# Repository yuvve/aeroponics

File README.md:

# aeroponics

## Project Structure

. \
├── arduino \
│   └── Sensor example code written with PlatformIO \
├── design \
│   └── Buck-converter PCB files\
├── docs \
│   ├── Diagrams \
│   ├── Failure mode and effect analysis  \
│   └── Bill of materials \
├── ESPHome \
│   ├── Readme with ESPHome instructions \
│   └── ESPHome code for the microcontrollers \
├── OpenHAB \
│   ├── OpenHAB configuration files \
│   ├── OpenHAB automation scripts \
│   └── OpenHAB UI definitions \
├── RPi \
│   ├── Mosquitto MQTT broker configuration files \
│   └── Mosquitto MQTT broker docker-compose \
└── Simulations \
    └── EC sensor SPICE simulation files for Cadence Capture CIS

## Notes

At the current state there is no EC-sensor that is done. However, there is a simulation file that has been made that is meant to be worked on so that it may one day meet specification for the rest of the project. Thease specifications include but are not limited to: being able to be powered by the given power source, not requireing negative source and have an output range between 0 - 3.3V as not to fry the microcontroller.

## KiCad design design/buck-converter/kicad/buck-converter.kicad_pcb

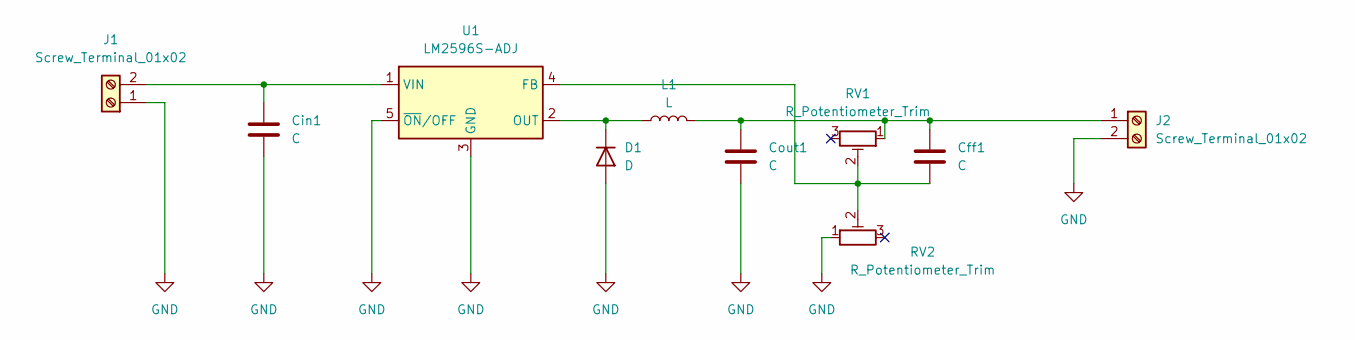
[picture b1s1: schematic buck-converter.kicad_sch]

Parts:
Cff1: C; TPME158K004R0015
Cin1: C; TPME158K004R0015
Cout1: C; TPME158K004R0015
D1: D; MBRS360T3G
J1, J2: Screw_Terminal_01x02; terminal-block-2-pole-TB006-508-02BE
L1: L; 36561040M101T
RV1, RV2: R_Potentiometer_Trim; Potentiometer_Bourns_3314J_Vertical
U1: LM2596S-ADJ; TO-263-5_TabPin3

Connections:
GND: Cin1.2, Cout1.2, D1.2 (A), J1.1, J2.2, RV2.1, U1.3 (GND), U1.5 (~ON/OFF)
unnamed: D1.1 (K), L1.1, U1.2 (OUT)
unnamed: Cin1.1, J1.2, U1.1 (VIN)
unnamed: Cff1.1, Cout1.1, J2.1, L1.2, RV1.1
unnamed: Cff1.2, RV1.2, RV2.2, U1.4 (FB)

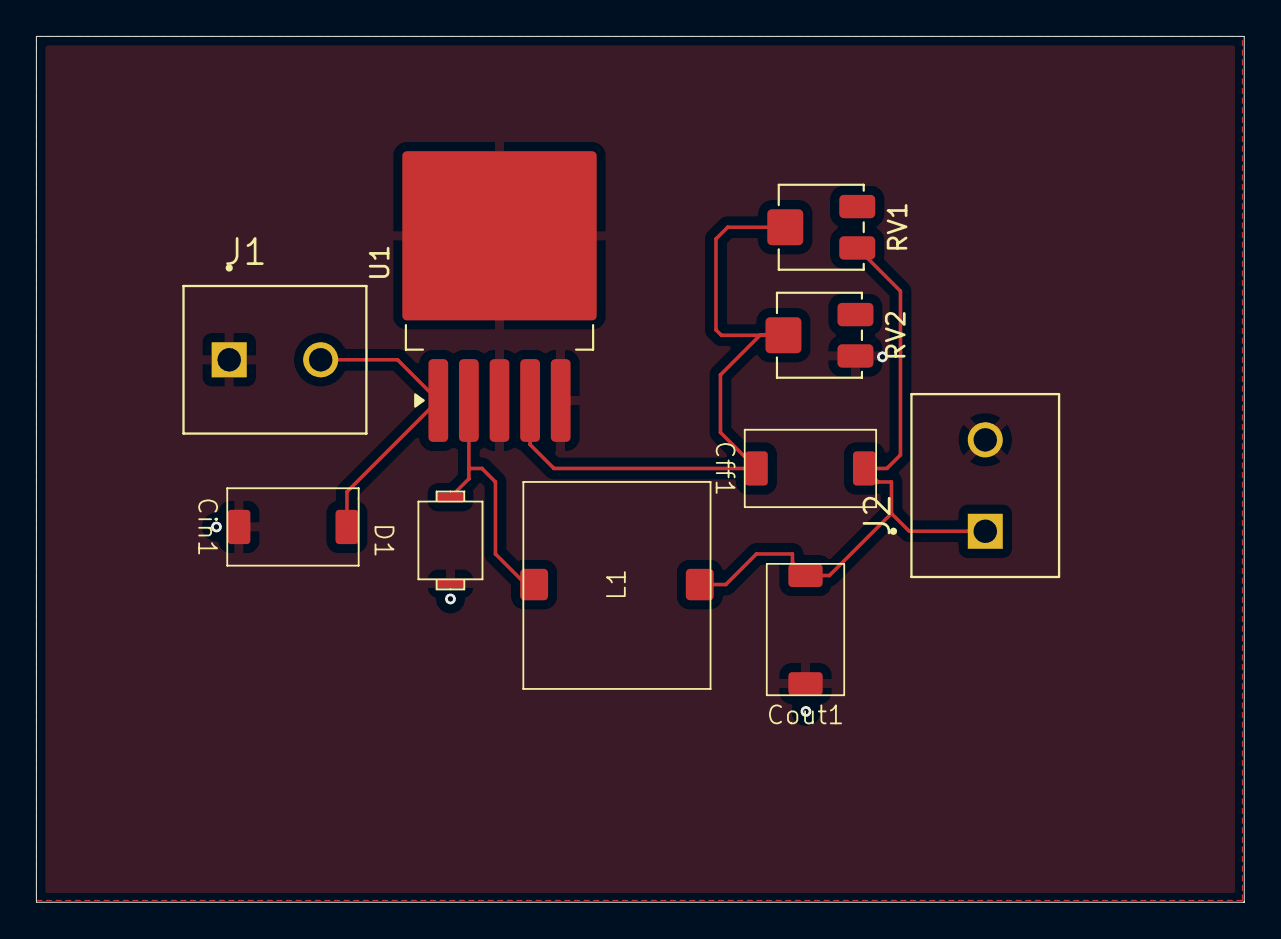
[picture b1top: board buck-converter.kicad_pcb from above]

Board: 2 copper layers, 67.1 x 48.1 mm, 10 parts (0 on the bottom side), 5 nets.

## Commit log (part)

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2025-09-03 Meeting notes #1
2025-09-03 Add meeting notes for plant selection and budget
2025-09-03 Add solution suggestions for growing systems
2025-09-03 Update meeting notes title and date
2025-09-03 Enhance vertical tower solution with sensor and control details
2025-09-03 Revise vertical tower solution suggestions
2025-09-03 Update meeting notes with solution suggestions
2025-09-05 Meeting notes from 2025-09-04
2025-09-05 Initial plan
2025-09-05 Meeting notes from 2025-09-05
2025-09-05 Made headers consistent for 2025-09-05 meeting notes.
2025-09-07 Meeting notes 2025-09-07
2025-09-07 Updated the meeting notes so that everything is visible in the preview
2025-09-08 Add meeting notes for September 8, 2025
2025-09-09 Add pump and tubing suggestions
2025-09-09 Update high-pressure system documentation with new link
    Added product link for micro line quick nozzles in Germany.
2025-09-10 Added links and some requirements for the tower
2025-09-10 Added some more product links
2025-09-10 Cleaned up the list
2025-09-10 Update product links in high-pressure system documentation
    Added new product links and updated existing ones for clarity.
2025-09-10 Update specifications and links in high-pressure system doc
2025-09-11 Added some 3 and 2 valves to the list of options
2025-09-11 Added some potential valves, accumulators and reservoirs
2025-09-11 Revise high-pressure system documentation with new products
    Updated product links and added new entries for misting nozzles, pressure tanks, tubing, and fittings.
2025-09-12 Create sensors.md
    Requirements, ideas, datasheets, etc.
2025-09-12 Create 2025-09-12.md
    Meeting notes for 2025-09-12.
2025-09-12 Update 2025-09-12.md
    Correcting grammar
2025-09-12 Update pump alternatives (only include pumps with built in pressure switches)
2025-09-14 Update tubing, add data sheets
2025-09-16 Update tower.md
    Added links to barrel, grow plugs and grow baskets
2025-09-16 Meeting notes 2025-09-16
2025-09-17 Initial draft
2025-09-17 Fix links
2025-09-17 Update high-pressure system documentation
2025-09-17 Update high-pressure system documentation with notes
2025-09-17 Add images
2025-09-17 Add functionality, dashboard alternatives
2025-09-18 Made preliminary purchasing list.
2025-09-18 Added preliminary purchasing list
2025-09-19 Added first batch purchasing list
2025-09-24 30 decide iot functionality (#38)
    * Initial draft
    * Add functionality, dashboard alternatives
    ---------
2025-09-24 8 choose high pressure equipment (#35)
    * Add pump and tubing suggestions
    * Add nozzle
    Updated the documentation to replace 'Alternatives' with 'Products' and added relevant product links.
    * Update high-pressure system documentation with new link
    Added product link for micro line quick nozzles in Germany.
    * Update product links in high-pressure system documentation
2025-09-24 Rename docs/controllers-computers.md to docs/parts/controllers-computers.md
2025-09-24 12 choose computation units microcontrollers and microprocessors (#40)
    * Create controllers-computers.md
    * Rename docs/controllers-computers.md to docs/parts/controllers-computers.md
    ---------
2025-09-24 10 choose sensors (#39)
    * Create sensors.md
    Requirements, ideas, datasheets, etc.
    * Added preliminary purchasing list
    * Added first batch purchasing list
    * Update sensors.md
    * Update sensors.md
2025-09-24 32 design or buy tower (#36)
    * Added links and some requirements for the tower
    * Added some more product links
    * Cleaned up the list
    * Update tower.md
    Added links to barrel, grow plugs and grow baskets
    * Update tower.md
2025-09-24 Component order done (#41)
2025-09-25 Add communication diagram
2025-09-25 Add workflow diagrams
2025-09-25 Fixed accidental mixup in names and added missing diagram
2025-09-26 Added diagram for power wiring.
2025-09-26 Added power diagrams.
2025-09-26 Added wheatstone bridge diagram.
2025-09-26 Restructured content.
2025-09-28 Updated diagrams
    Removed signal wires and added the Raspberry Pi to the diagram with a separate power supply.
2025-09-29 Add drainage to component order
2025-09-29 Add workflow diagrams (#44)
    * Add workflow diagrams
    * Fixed accidental mixup in names and added missing diagram
2025-09-29 Update component order and water diagram
2025-09-29 fixed design
2025-09-30 Initial commit for remote server and mosquitto
2025-09-30 Fix gitignore
2025-10-02 Update sensor diagrams
    Updated sensor diagrams in accordance with the PR review.
    Ref: #45
2025-10-02 Add ec sensor diagrams
2025-10-02 Update ec sensor diagrams
2025-10-05 Add four prong ec sensor diagram
2025-10-05 Add sonic-sensor.ino
    Added first draft of sonic sensor Arduino code to get the distance (for
    the water level measurement in the water tank).
2025-10-07 Add ESPHome
2025-10-07 Ignore esphome data folder, change secrets example name
2025-10-07 Add ESPHome readme
2025-10-07 Remove OpenHAB docker, add symlink to conf folder instead
2025-10-07 Fix wrong symlink direction
2025-10-07 Update sonic sensor
    Restructured subdirectories, changed mainfile
2025-10-07 Update temperature sensor
    Created subdirectory structure, created temperature-sensor.cpp
2025-10-09 47 new drainage solution (#48)
    * Add drainage to component order
    * Update component order and water diagram
    * Increase font size in water diagram
    * fixed design
    ---------
2025-10-10 Add communication diagram (#46)
2025-10-10 37 power wiring diagram (#45)
    * Added diagram for power wiring.
    * Added power diagrams.
    * Added wheatstone bridge diagram.
    * Restructured content.
    * Updated diagrams
    Removed signal wires and added the Raspberry Pi to the diagram with a separate power supply.
2025-10-10 Add mqtt diagram
2025-10-15 Update ESPHome
2025-10-15 Add tower 1 item yaml definitions
2025-10-16 MQTT tower1 -> tower/1, actuator -> control, add sensors for actuators status
2025-10-16 Add rust client in progress
2025-10-27 Add missing MQTT broker config
2025-10-27 Replace DSL with YAML, add channels
2025-10-27 Remove clientid from mqtt broker definition
2025-10-27 Use tailscale magic DNS instead of IP in mqtt broker config
2025-10-27 Add item-channel links
2025-10-27 Update channels to match MQTT diagram
2025-10-27 Fix incorrect channel labels
2025-10-27 Update diagrams
    Made microcontroller diagrams
2025-10-27 Update Rust Dashboard
2025-10-31 Sensor updating works
2025-11-03 MQTT bridge mode true
2025-11-03 Dashboard sensors working
2025-11-07 Sync changes
2025-11-09 sync between machines
2025-11-09 Update diagram
2025-11-09 Remove lower tower microcontroller
2025-11-09 31 create remote server (#53)
    * Initial commit for remote server and mosquitto
    * Fix gitignore
    * Add ESPHome
    * Ignore esphome data folder, change secrets example name
    * Add ESPHome readme
    * Remove OpenHAB docker, add symlink to conf folder instead
2025-11-09 Remove lower tower from mqtt diagram
2025-11-09 Progressed with rewrite
2025-11-11 Add additional solenoid actuator and clarify names
2025-11-11 Add additional solenoid actuator and clarify names (#61)
2025-11-11 Fix humidity UI label
2025-11-11 Add overview UI
2025-11-11 Fix item units
2025-11-11 Fix channel name mismatch
2025-11-11 Add unit to EC
2025-11-11 Update alert ranges
2025-11-11 Rewrite 2
2025-11-11 Let Towers do MQTT instead of Tower
2025-11-14 Update humidity-sensor
    Added code for humidity sensor, outputs frequency
2025-11-14 Update humidity-sensor
    Updated main.cpp, fixed conversion error
2025-11-14 added the pH-sensor for ESP32
2025-11-14 Update microcontroller.png
    Updated microcontroller.png and microcontroller.drawio
2025-11-14 Update microcontroller.png
    Fixed supply values and added note about pH sensor.
2025-11-19 Add water-level sensor
2025-11-20 Add solenoid and pump sensor/control
2025-11-20 Fix solenoid and pump MQTT payload
2025-11-24 Add fmea.ods
    Added FMEA template.
2025-11-24 Create buck-converter directory
    KiCad initial creation
2025-11-24 Added files via upload
2025-11-24 Update buck-converter kicad
2025-11-25 Add pressure delay and watchdog
2025-11-25 Create footprint
    Create footprint for 36561040M101T SMD inductor
2025-11-25 Add TPME158K004R0015.kicad_mod
    Added a footprint for the tantalum low ESR capacitor from KYOCERA AVX
2025-11-25 Add MBRS360T3G.kicad_mod
    Added a footprint for the MBRS360T3G low ESR capacitor
2025-11-25 Add terminal-block-2-pole-TB006-508-02BE.kicad_mod
    Added a connector footprint, borrowed from the E7009E course room.
2025-11-25 Update KiCad schematics
    Updated footprints, added PCB
2025-11-27 Add tower sensors
2025-11-27 Add ph sensor
2025-11-27 Add humidity sensor
2025-11-27 Add pressure sensor
2025-11-28 Fix pump delay sequence
2025-11-28 60 work on UI openhab dashboard (#62)
    * Add overview UI
    * Fix item units
    * Fix humidity UI label
    * Fix channel name mismatch
    * Add unit to EC
    * Update alert ranges
2025-11-28 Add alerts to yaml config
2025-11-28 Fix wrong label
2025-11-28 Fix wrong Dimension name
2025-12-02 Add alerts toggle
2025-12-02 Add all alerts
2025-12-02 Fix missing tower number in description
2025-12-02 Fix wrong trigger variable
2025-12-03 Add test yaml
2025-12-03 Add ph reading using internal ADC
2025-12-03 Reduce humidity interval
2025-12-05 Update ph to native ESP Home
2025-12-05 Add common and pins yaml
2025-12-05 Remove test yaml
2025-12-05 Remove calibration topics
2025-12-08 Fix bad automation rules
2025-12-08 Change unit of measurement for pressure
2025-12-08 Fix EC sensor wrong dimension and wrong names in automation scripts
2025-12-08 Initial commit of EC sensor simulation files
2025-12-08 fmpa
2025-12-08 Fix conditional formatting and formulas
2025-12-17 Add calibration
2025-12-19 Update mqtt diagram
2025-12-21 Add input validation on solenoid MQTT commands
2025-12-23 68 implement alerts (#70)
    * Add alerts to yaml config
    * Fix wrong label
    * Fix wrong Dimension name
    * Update overview.yaml
    * Add alerts toggle
    * Add all alerts
2026-01-08 Create directory PlatformIO
    Moved the sensor directories into PlatformIO for clarity
2026-01-11 Add mqtt diagram (#51)
    * Add mqtt diagram
    * MQTT tower1 -> tower/1, actuator -> control, add sensors for actuators status
    * Remove lower tower from mqtt diagram
    * Add additional solenoid actuator and clarify names
    * Fix 'sensor' instead of 'control'
    * Update mqtt diagram
2026-01-11 16 program microcontrollers (#74)
    * Added diagram for power wiring.
    * Added power diagrams.
    * Added wheatstone bridge diagram.
    * Restructured content.
    * Updated diagrams
    Removed signal wires and added the Raspberry Pi to the diagram with a separate power supply.
2026-01-11 63 perform failure mode and effects analysis fmea (#75)
    * Add fmea.ods
    Added FMEA template.
    * Add files via upload
    * fmpa
    * Fix conditional formatting and formulas
    ---------
2026-01-11 54 create microcontroller diagrams (#76)
    * Update diagrams
    Made microcontroller diagrams
    * Update microcontroller.png
    Updated microcontroller.png and microcontroller.drawio
    * Update microcontroller.png
    Fixed supply values and added note about pH sensor.
2026-01-11 Update README with EC sensor current state
    Added current state information about the EC sensor and its specifications.
2026-01-11 49 design ec sensor (#77)
    * Add ec sensor diagrams
    * Update ec sensor diagrams
    * Add four prong ec sensor diagram
    * Initial commit of EC sensor simulation files
    * Update README with EC sensor current state
    Added current state information about the EC sensor and its specifications.
2026-01-12 Add footprints
    Pushing updates to footprints
2026-01-12 64 create kicad file for buck converter (#78)
    * Create buck-converter directory
    KiCad initial creation
    * Added files via upload
    * Update buck-converter kicad
    * Create footprint
    Create footprint for 36561040M101T SMD inductor
2026-01-13 Update comm diagram
2026-01-13 Update comm diagram (#79)
